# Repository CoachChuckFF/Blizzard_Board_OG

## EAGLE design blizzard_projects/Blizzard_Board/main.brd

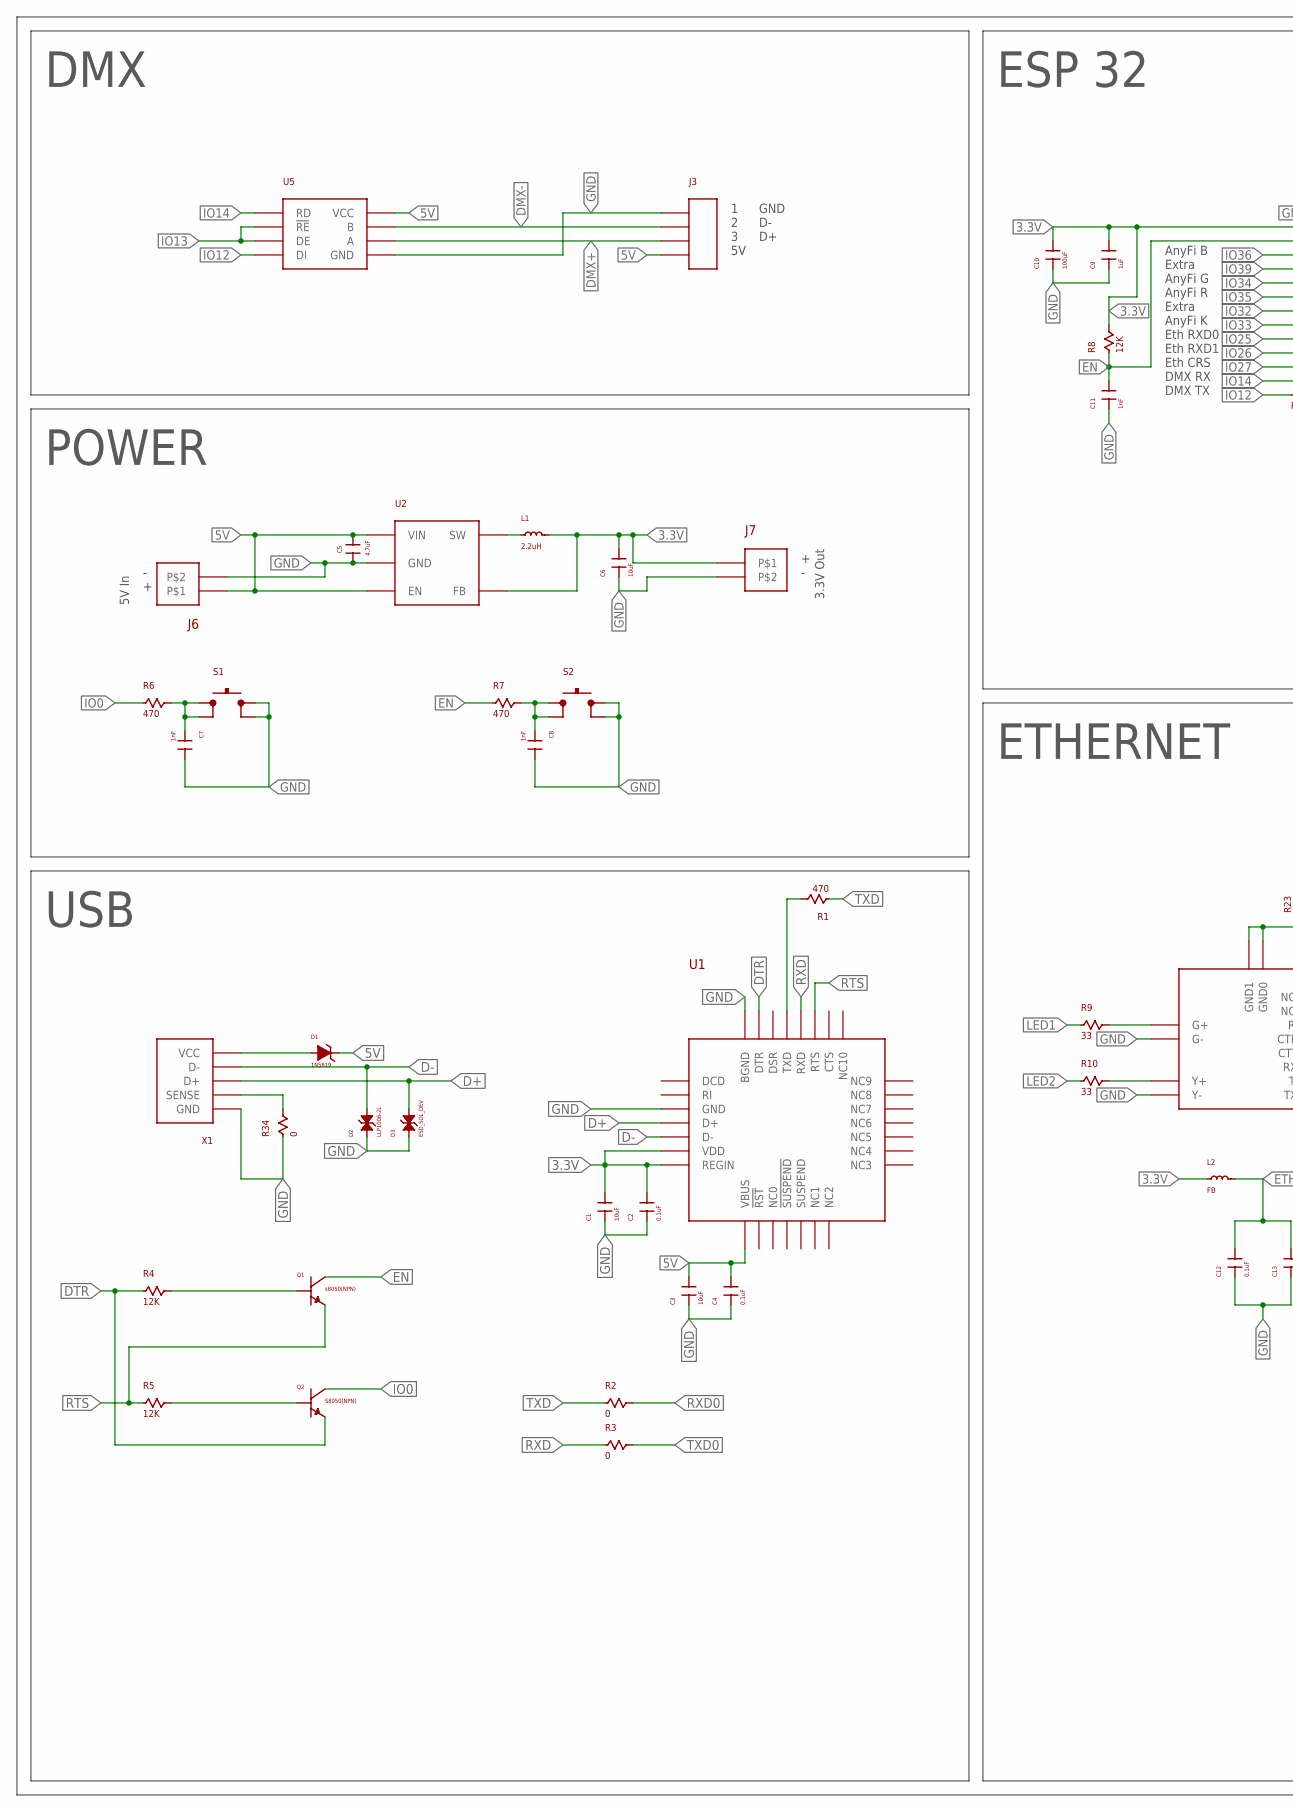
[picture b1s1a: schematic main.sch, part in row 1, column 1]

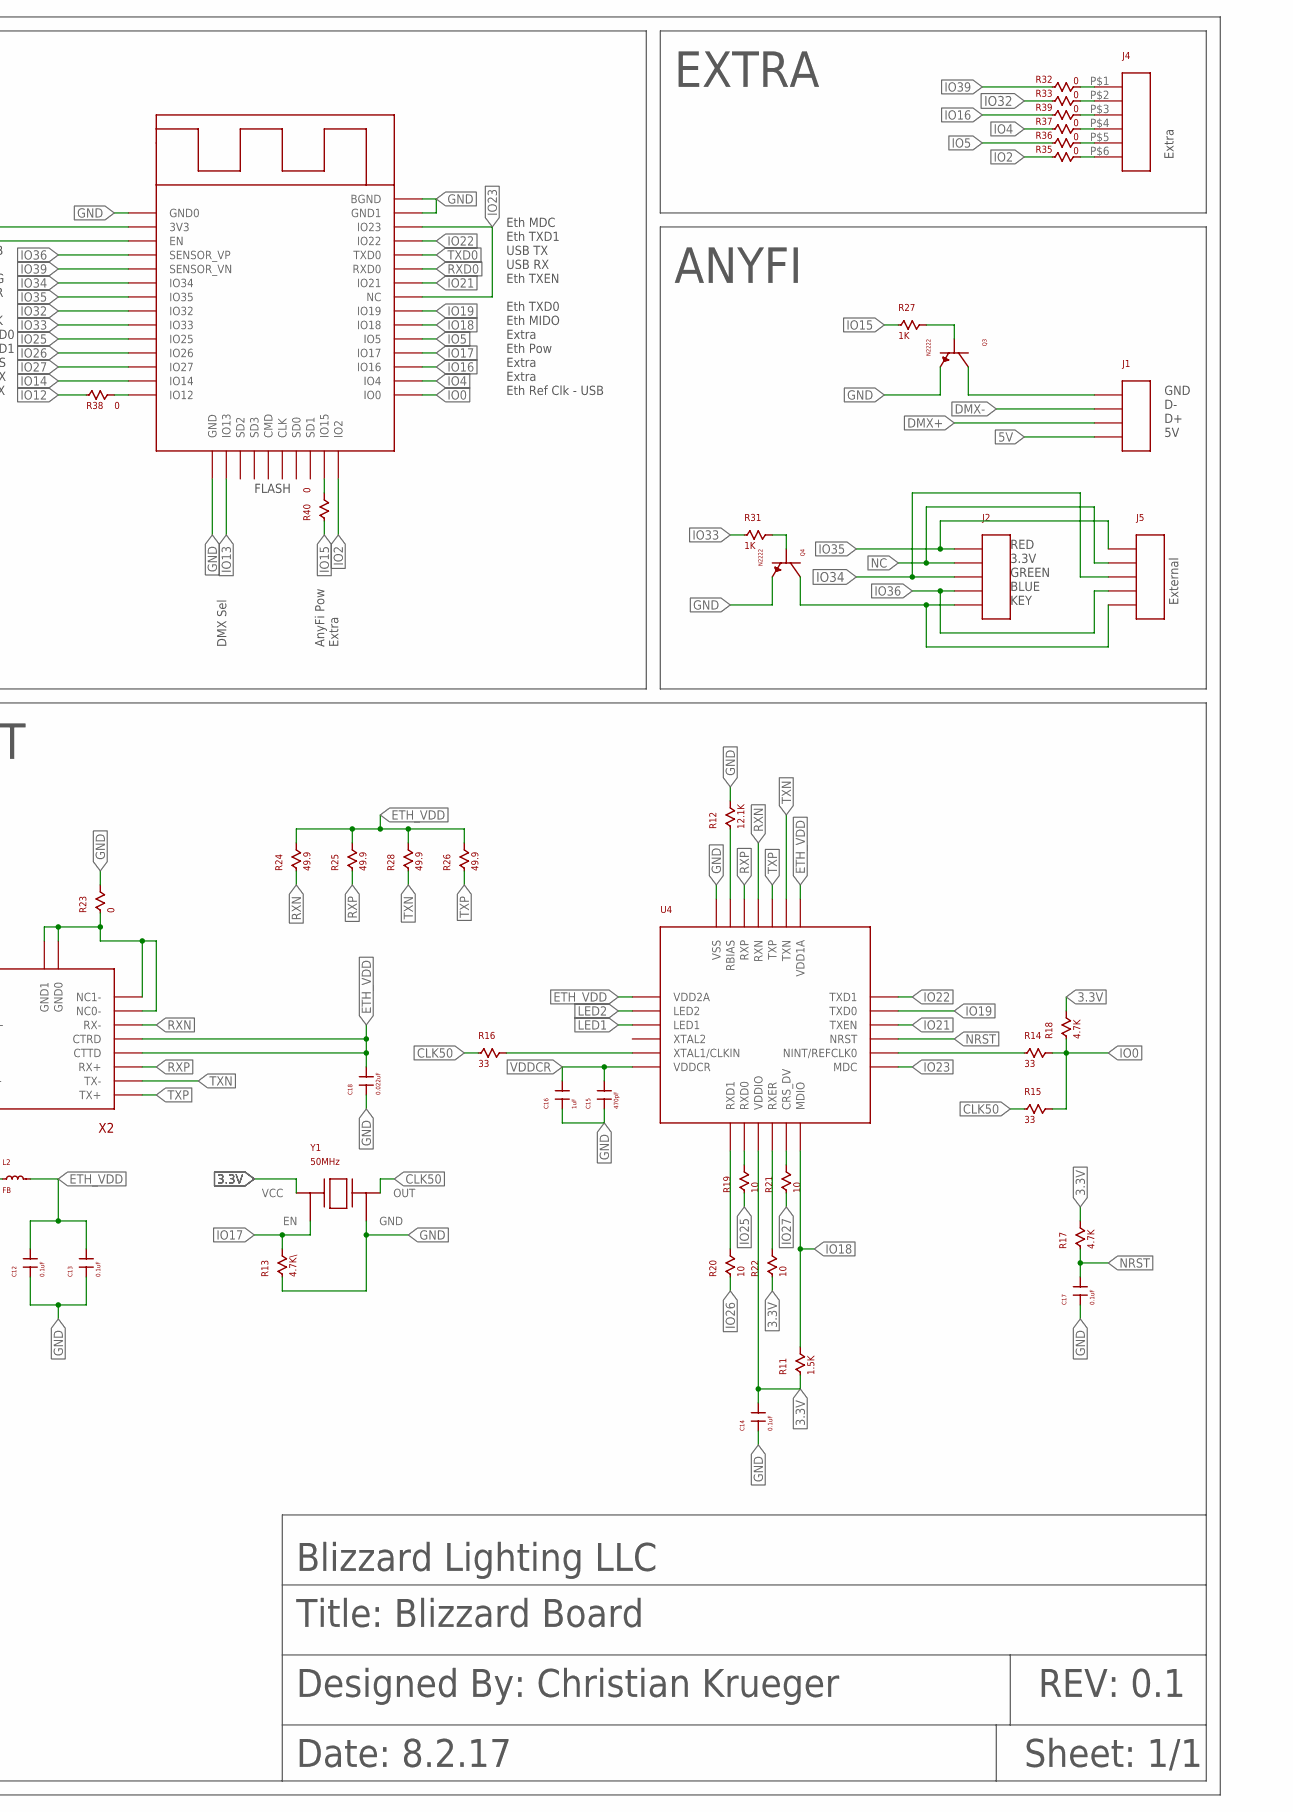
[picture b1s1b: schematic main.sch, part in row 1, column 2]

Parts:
C1, C3, C6: 10uF; 0805_PKG
C2, C4, C12, C13, C14, C17: 0.1uF; 0805_PKG
C5: 4.7uF; 0805_PKG
C7, C8, C11: 1nF; 0805_PKG
C9, C16: 1uF; 0805_PKG
C10: 100uF; 0805_PKG
C15: 470pF; 0805_PKG
C18: 0.022uF; 0805_PKG
D1: 1N5819; ZENER_PKG
D2: LLP1006-2L; ESD_SOL_PKG
D3: ESD_SOL_DEV; ESD_SOL_PKG
J1, J3: XH_4POS_DEV; XH_4POS_PKG
J2, J5: XH_5POS_DEV; XH_5POS_PKG
J4: XH_6POS_DEV; XH_6POS_PKG
J6, J7: XH_2POS_DEV; XH_2POS_PKG
L1: 2.2uH; 0805_PKG
L2: FB; 0805_PKG
Q1: s8050(NPN); SOT_23_3_PKG
Q2: S8050(NPN); SOT_23_3_PKG
Q3, Q4: N2222; SOT_23_3_PKG
R1, R6, R7: 470; 0805_PKG
R2, R3, R23, R32, R33, R34, R35, R36, R37, R38, R39, R40: 0; 0805_PKG
R4, R5, R8: 12K; 0805_PKG
R9, R10, R14, R15, R16: 33; 0805_PKG
R11: 1.5K; 0805_PKG
R12: 12.1K; 0805_PKG
R13: 4.7K\; 0805_PKG
R17, R18: 4.7K; 0805_PKG
R19, R20, R21, R22: 10; 0805_PKG
R24, R25, R26, R28: 49.9; 0805_PKG
R27, R31: 1K; 0805_PKG
S1, S2: TACTILE_PB_DEV; TACKTILE_PB_PKG
U1: USB_TO_UART_DEV; QFN_28_PKG
U2: BUCK_CONVERTER_DEV; SOT_23_PKG
U3: ESP_WROOM_32_DEV; ESP_WROOM_32_PKG
U4: LAN8720_DEV; QFN_24_PKG
U5: MAX_485_DEV; MAX_485_PKG
X1: USB_CONN_DEV; USB_CONN_PKG
X2: ETHERNET_DEV; ETHERNET_PKG
Y1: 50MHz; OSC_PKG

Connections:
3.3V: C1.P$2, C2.P$2, C6.P$2, C9.P$2, C10.P$2, C14.P$2, J7.P$1, L1.P$2, L2.P$1, R8.P$2, R11.P$1, R17.P$2, R18.P$2, R22.P$1, U1.REGIN, U1.VDD, U2.4 (FB), U3.3V3, U4.9 (VDDIO), Y1.4 (VCC)
5V: C3.P$2, C4.P$2, C5.P$2, D1.P$2, J1.P$4, J3.P$4, J6.P$1, U1.VBUS, U2.1 (VIN), U2.3 (EN), U5.P$8 (VCC)
CLK50: R15.P$1, R16.P$1, Y1.3 (OUT)
D+: D3.P$2, U1.D+, X1.PIN3 (D+)
D-: D2.P$2, U1.D-, X1.PIN2 (D-)
DMX+: J1.P$3, J3.P$3, U5.P$6 (A)
DMX-: J1.P$2, J3.P$2, U5.P$7 (B)
DTR: Q2.P$2 (E), R4.P$1, U1.DTR
EN: C11.P$2, Q1.P$3 (C), R7.P$1, R8.P$1, U3.EN
ETH_VDD: C12.P$2, C13.P$2, C18.P$2, L2.P$2, R24.P$2, R25.P$2, R26.P$2, R28.P$2, U4.1 (VDD2A), U4.19 (VDD1A), X2.4 (CTTD), X2.5 (CTRD)
GND: C1.P$1, C2.P$1, C3.P$1, C4.P$1, C5.P$1, C6.P$1, C7.P$2, C8.P$2, C9.P$1, C10.P$1, C11.P$1, C12.P$1, C13.P$1, C14.P$1, C15.P$1, C16.P$1, C17.P$1, C18.P$1, D2.P$1, D3.P$1, J3.P$1, J6.P$2, J7.P$2, Q3.P$2 (E), Q4.P$2 (E), R12.P$2, R13.P$1, R23.P$2, R34.P$2, S1.3, S1.4, S2.3, S2.4, U1.BGND, U1.GND, U2.2 (GND), U3.BGND, U3.GND0 (GND), U3.GND1 (GND0), U3.GND2 (GND1), U4.BGND (VSS), U5.P$5 (GND), X1.PIN4 (SENSE), X2.G-, X2.Y-, Y1.2 (GND)
IO0: Q2.P$3 (C), R6.P$1, R14.P$2, R15.P$2, R18.P$1, U3.IO0
IO2: R35.P$1, U3.IO2
IO4: R37.P$1, U3.IO4
IO5: R36.P$1, U3.IO5
IO12: R38.P$1, U5.P$4 (DI)
IO13: U3.IO13, U5.P$2 (!RE), U5.P$3 (DE)
IO14: U3.IO14, U5.P$1 (RD)
IO15: R27.P$1, R40.P$1
IO16: R39.P$1, U3.IO16
IO17: R13.P$2, U3.IO17, Y1.1 (EN)
IO18: R11.P$2, U3.IO18, U4.12 (MDIO)
IO19: U3.IO19, U4.17 (TXD0)
IO21: U3.IO21, U4.16 (TXEN)
IO22: U3.IO22, U4.18 (TXD1)
IO23: U3.IO23, U3.NC, U4.13 (MDC)
IO25: R19.P$1, U3.IO25
IO26: R20.P$1, U3.IO26
IO27: R21.P$1, U3.IO27
IO32: R33.P$1, U3.IO32
IO33: R31.P$1, U3.IO33
IO34: J2.P$3, J5.P$3, U3.IO34
IO35: J2.P$1, J5.P$1, U3.IO35
IO36: J2.P$4, J5.P$4, U3.SENSOR_VP
IO39: R32.P$1, U3.SENSOR_VN
LED1: R9.P$1, U4.3 (LED1)
LED2: R10.P$1, U4.2 (LED2)
unnamed: J4.P$1, R32.P$2
unnamed: J4.P$2, R33.P$2
unnamed: R1.P$2, U1.TXD
unnamed: D1.P$1, X1.PIN1 (VCC)
unnamed: Q1.P$1 (B), R4.P$2
unnamed: Q2.P$1 (B), R5.P$2
unnamed: L1.P$1, U2.5 (SW)
unnamed: R34.P$1, X1.PIN5 (GND)
unnamed: J4.P$3, R39.P$2
unnamed: J4.P$4, R37.P$2
unnamed: J4.P$5, R36.P$2
unnamed: J4.P$6, R35.P$2
unnamed: R38.P$2, U3.IO12
unnamed: R40.P$2, U3.IO15
unnamed: R9.P$2, X2.G+
unnamed: C7.P$1, R6.P$2, S1.1, S1.2
unnamed: R22.P$2, U4.10 (RXER)
unnamed: R10.P$2, X2.Y+
unnamed: C8.P$1, R7.P$2, S2.1, S2.2
unnamed: R12.P$1, U4.24 (RBIAS)
unnamed: R16.P$2, U4.5 (XTAL1/CLKIN)
unnamed: R14.P$1, U4.14 (NINT/REFCLK0)
unnamed: R20.P$2, U4.7 (RXD1)
unnamed: R19.P$2, U4.8 (RXD0)
unnamed: R21.P$2, U4.11 (CRS_DV)
unnamed: R23.P$1, X2.7 (NC0-), X2.8 (NC1-), X2.GND0, X2.GND1
unnamed: J1.P$1, Q3.P$3 (C)
unnamed: J2.P$5, J5.P$5, Q4.P$3 (C)
unnamed: Q4.P$1 (B), R31.P$2
unnamed: Q3.P$1 (B), R27.P$2
NC: J2.P$2, J5.P$2
NRST: C17.P$2, R17.P$1, U4.15 (NRST)
RTS: Q1.P$2 (E), R5.P$1, U1.RTS
RXD: R3.P$1, U1.RXD
RXD0: R2.P$2, U3.RXD0
RXN: R24.P$1, U4.22 (RXN), X2.6 (RX-)
RXP: R25.P$1, U4.23 (RXP), X2.3 (RX+)
TXD: R1.P$1, R2.P$1
TXD0: R3.P$2, U3.TXD0
TXN: R28.P$1, U4.20 (TXN), X2.2 (TX-)
TXP: R26.P$1, U4.21 (TXP), X2.1 (TX+)
VDDCR: C15.P$2, C16.P$2, U4.6 (VDDCR)

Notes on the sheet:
USB
POWER
ETHERNET
GND
RED
3.3V
GREEN
BLUE
KEY
AnyFi B
Extra
Eth CRS
Eth Pow
AnyFi R
AnyFi G
AnyFi K
Eth RXD0
Eth RXD1
DMX RX
DMX TX
DMX Sel
AnyFi Pow
FLASH
Eth Ref Clk - USB
Eth MIDO
Eth TXD0
Eth TXEN
Eth TXD1
USB TX
USB RX
Eth MDC
DMX
ESP 32
EXTRA
External
ANYFI
5V In
3.3V Out
Title: Blizzard Board
Designed By: Christian Krueger

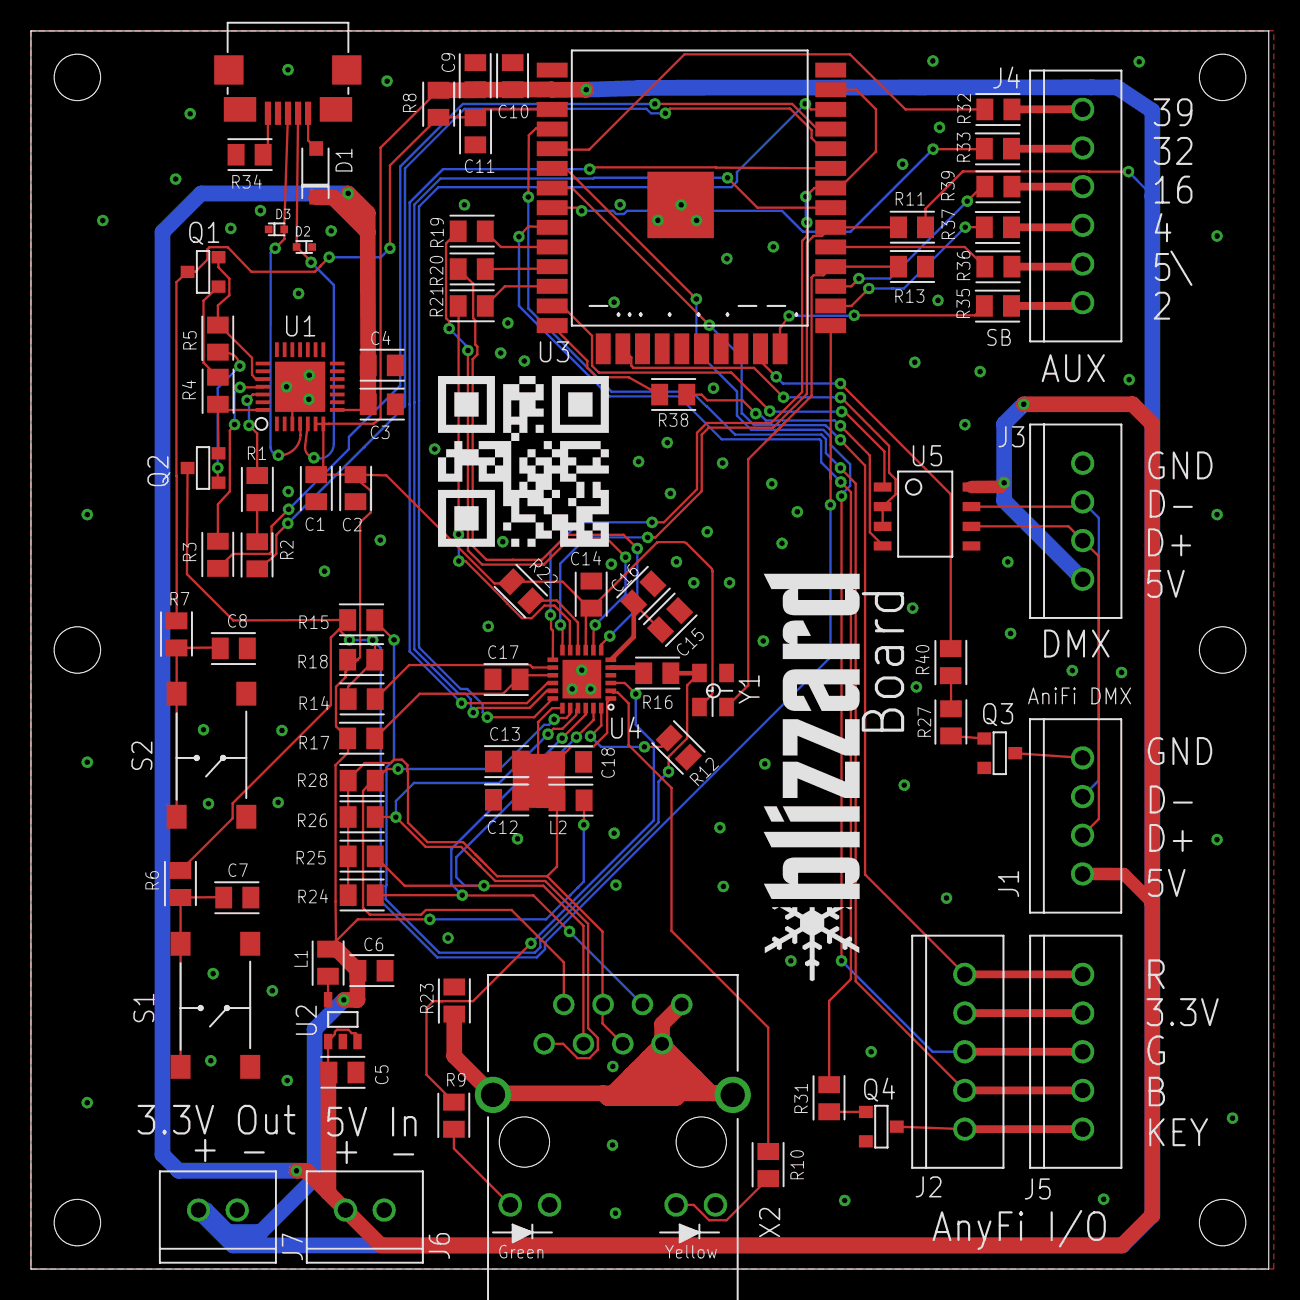
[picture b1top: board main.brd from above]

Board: 2 copper layers, 80.0 x 80.0 mm, 82 parts (0 on the bottom side), 79 nets.

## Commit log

2017-07-31 first
2017-08-02 libs done-ish
2017-08-02 rev1 sch done
2017-08-03 started tracing
2017-08-04 finished tracing
2017-08-04 v1 out to order
2017-08-04 v1 out to order p2
2017-08-08 waiting on first order
2017-08-16 sent 1st order
2017-08-28 REV 1.2
2017-08-30 version 1.2
